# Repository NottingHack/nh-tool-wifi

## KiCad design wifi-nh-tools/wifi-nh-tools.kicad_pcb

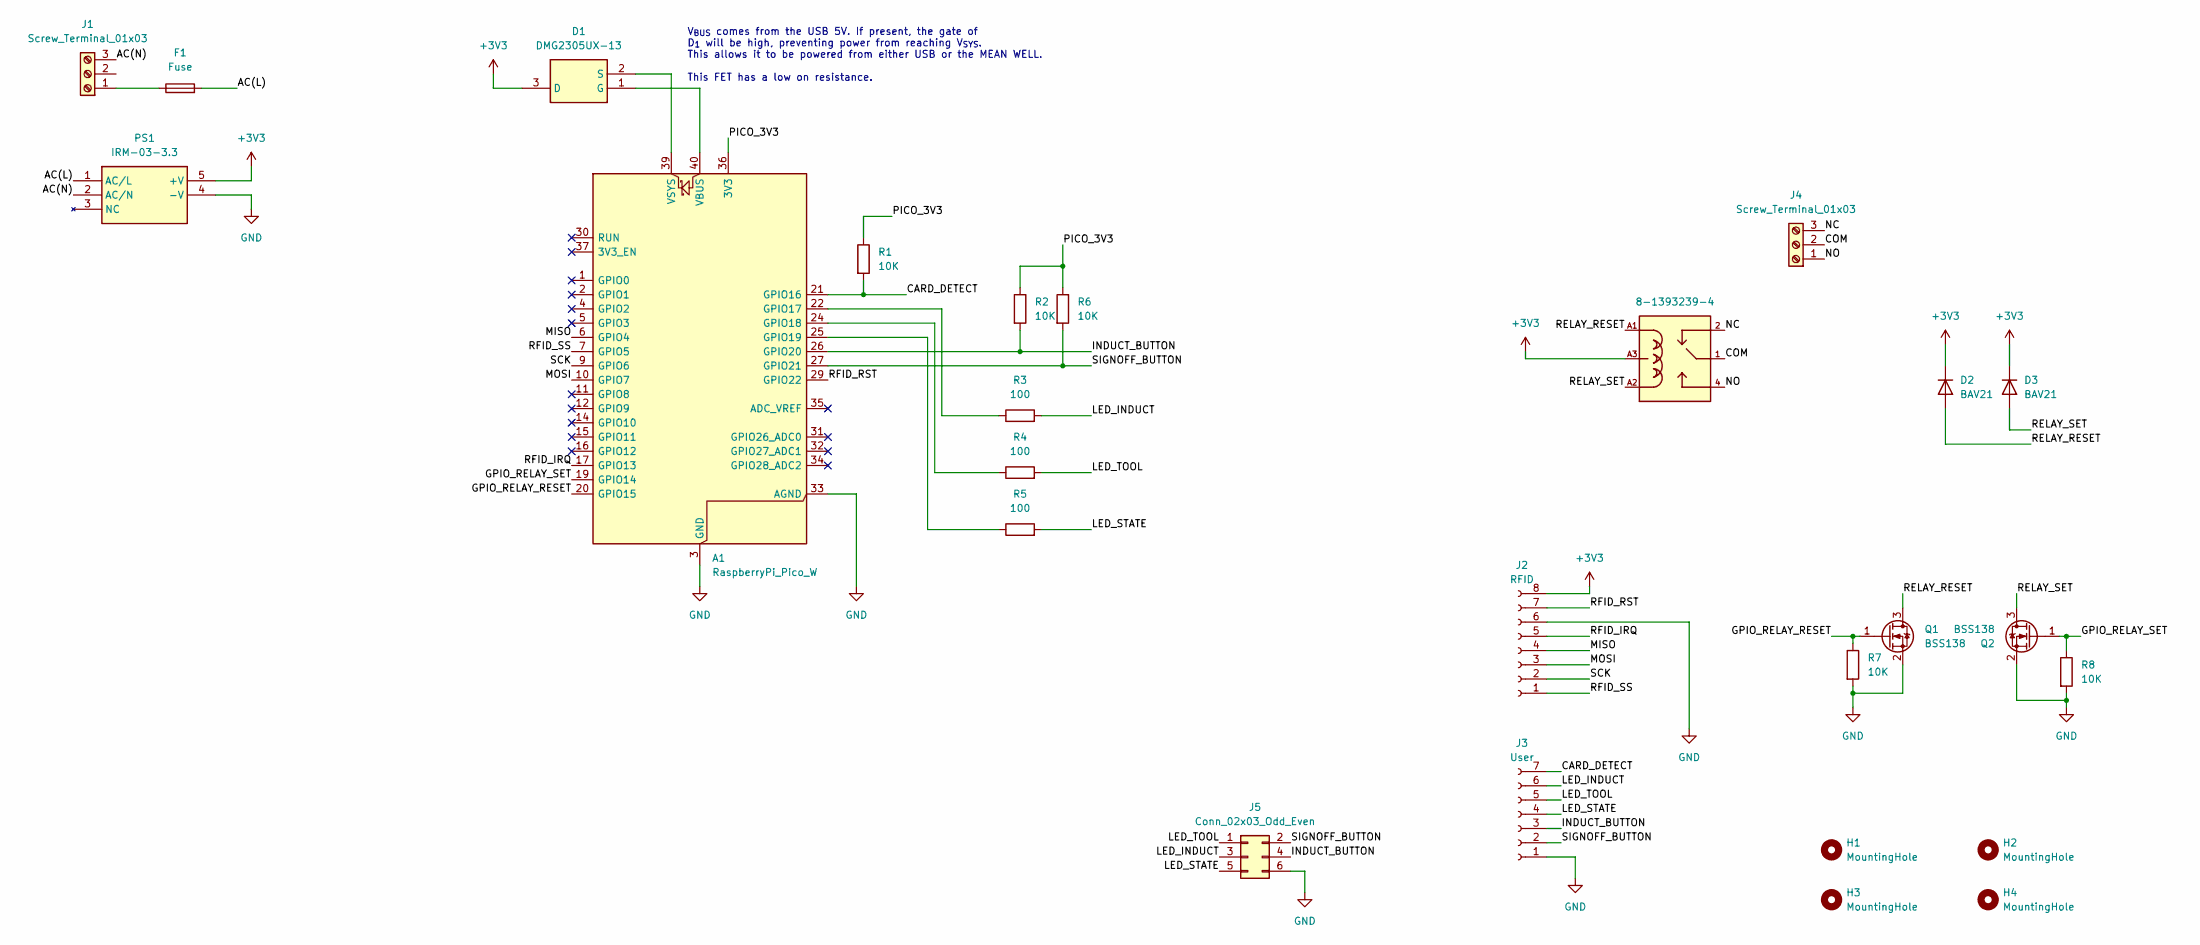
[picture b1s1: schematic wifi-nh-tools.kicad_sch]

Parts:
A1: RaspberryPi_Pico_W; RaspberryPi_Pico_W_SMD_HandSolder
D1: DMG2305UX-13; SOT96P240X120-3N; MPN DMG2305UX-13
D2, D3: BAV21; Nexperia_CFP3_SOD-123W; MPN BAV21WS-AQ
F1: Fuse; Fuse_Littelfuse-NANO2-462; MPN 0443002.DR
H1, H2, H3, H4: MountingHole; MountingHole_3.2mm_M3
J1, J4: Screw_Terminal_01x03; TerminalBlock_WAGO_2601-1103_1x03_P3.50mm_Horizontal; MPN 2601-1103
J2: RFID; PinSocket_1x08_P2.54mm_Vertical; MPN 61900811121
J3: User; PinSocket_1x07_P2.54mm_Vertical; MPN 61900811121
J5: Conn_02x03_Odd_Even; PinSocket_2x03_P2.54mm_Vertical; MPN 61303218421
K1: 8-1393239-4; TE_8-1393239-4; MPN 8-1393239-4
PS1: IRM-03-3.3; IRM035; MPN IRM-03-3.3
Q1, Q2: BSS138; SOT-23; MPN BSS138
R1, R2, R6: 10K; R_0603_1608Metric
R3, R4, R5: 100; R_0603_1608Metric
R7, R8: 10K; R_0603_1608Metric; MPN 560112116005

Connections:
+3V3: D1.3 (D), D2.1 (K), D3.1 (K), J2.8, K1.A3, PS1.5 (+V)
/AC(L): F1.2, PS1.1 (AC/L)
/AC(N): J1.3, PS1.2 (AC/N)
/CARD_DETECT: A1.21 (GPIO16), J3.7, R1.2
/COM: J4.2, K1.1, K1.11
/GPIO_RELAY_RESET: A1.20 (GPIO15), Q1.1 (G), R7.1
/GPIO_RELAY_SET: A1.19 (GPIO14), Q2.1 (G), R8.1
/INDUCT_BUTTON: A1.26 (GPIO20), J3.3, J5.4, R2.2
/LED_INDUCT: J3.6, J5.3, R3.2
/LED_STATE: J3.4, J5.5, R5.2
/LED_TOOL: J3.5, J5.1, R4.2
/MISO: A1.6 (GPIO4), J2.4
/MOSI: A1.10 (GPIO7), J2.3
/NC: J4.3, K1.2, K1.12
/NO: J4.1, K1.4, K1.14
/PICO_3V3: A1.36 (3V3), R1.1, R2.1, R6.1
/RELAY_RESET: D2.2 (A), K1.A1, Q1.3 (D)
/RELAY_SET: D3.2 (A), K1.A2, Q2.3 (D)
/RFID_IRQ: A1.17 (GPIO13), J2.5
/RFID_RST: A1.29 (GPIO22), J2.7
/RFID_SS: A1.7 (GPIO5), J2.1
/SCK: A1.9 (GPIO6), J2.2
/SIGNOFF_BUTTON: A1.27 (GPIO21), J3.2, J5.2, R6.2
GND: A1.3 (GND), A1.8 (GND), A1.13 (GND), A1.18 (GND), A1.23 (GND), A1.28 (GND), A1.33 (AGND), A1.38 (GND), J2.6, J3.1, J5.6, PS1.4 (-V), Q1.2 (S), Q2.2 (S), R7.2, R8.2
unnamed: A1.22 (GPIO17), R3.1
unnamed: A1.24 (GPIO18), R4.1
unnamed: A1.25 (GPIO19), R5.1
unnamed: A1.40 (VBUS), D1.1 (G)
unnamed: A1.39 (VSYS), D1.2 (S)
unnamed: F1.1, J1.1

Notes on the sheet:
V_{BUS} comes from the USB 5V. If present, the gate of D_{1} will be high, preventing power from reaching V_{SYS}. This allows it to be powered from either USB or the MEAN WELL. This FET has a low on resistance.

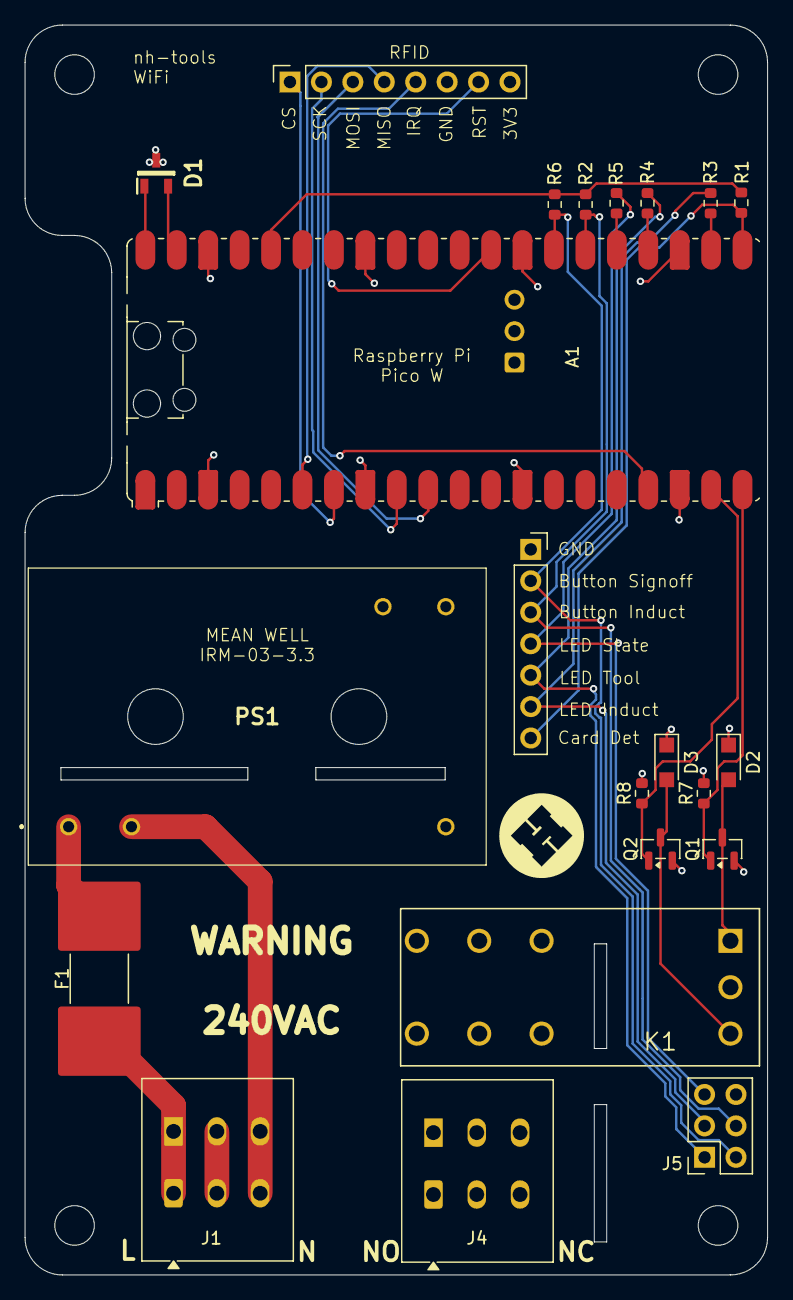
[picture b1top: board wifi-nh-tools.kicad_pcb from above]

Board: 4 copper layers, 60.0 x 101.0 mm, 26 parts (0 on the bottom side), 30 nets.

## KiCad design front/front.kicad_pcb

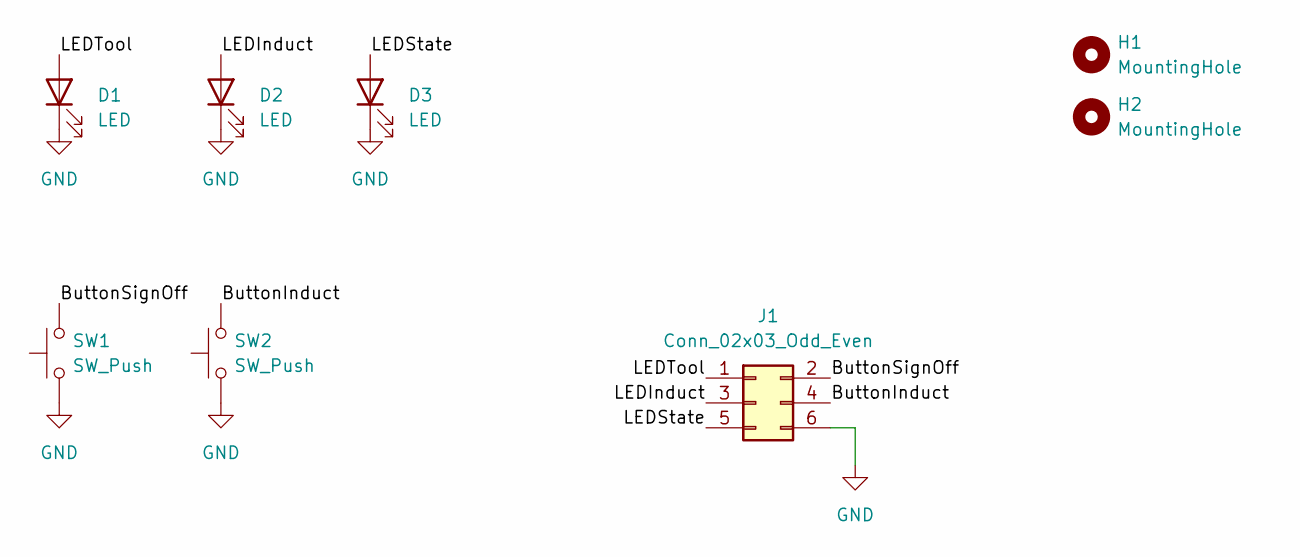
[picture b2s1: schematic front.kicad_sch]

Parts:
D1, D2, D3: LED; LED_D5.0mm
H1, H2: MountingHole; MountingHole_3.2mm_M3
J1: Conn_02x03_Odd_Even; PinHeader_2x03_P2.54mm_Vertical; MPN 61303218421
SW1, SW2: SW_Push; SW_PUSH_6mm

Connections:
/ButtonInduct: J1.4, SW2.2
/ButtonSignOff: J1.2, SW1.2
/LEDInduct: D2.2 (A), J1.3
/LEDState: D3.2 (A), J1.5
/LEDTool: D1.2 (A), J1.1
GND: D1.1 (K), D2.1 (K), D3.1 (K), J1.6, SW1.1, SW2.1

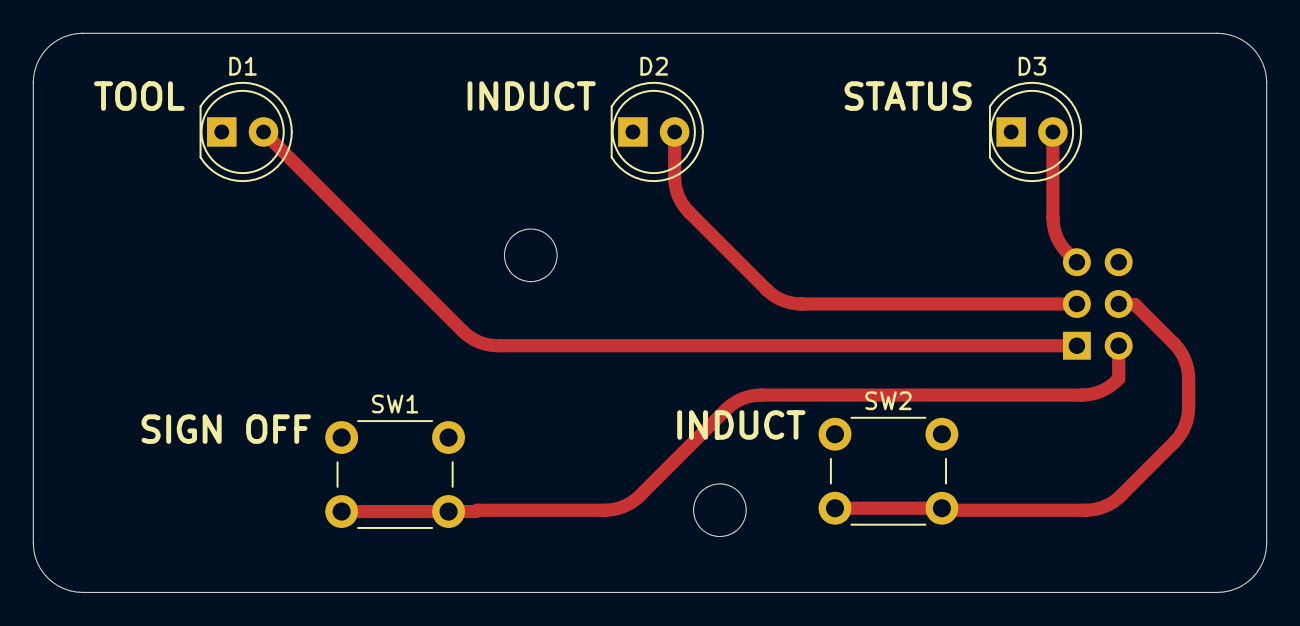
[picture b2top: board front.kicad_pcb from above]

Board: 2 copper layers, 75.0 x 34.0 mm, 8 parts (1 on the bottom side), 6 nets.

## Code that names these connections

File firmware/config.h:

#pragma once

#define WIFI_SSID ""
#define WIFI_PASSWORD ""

#define IP_ADDRESS ""
#define MQTT_ADDRESS ""
#define MQTT_BASE_TOPIC ""
#define TOOL_NAME ""

#define PIN_MISO 4
#define PIN_MOSI 7
#define PIN_SCK 6

#define PIN_RFID_SS 5
#define PIN_RFID_IRQ 13
#define PIN_RFID_RESET 22

#define PIN_RELAY_SET 14
#define PIN_RELAY_RESET 15

#define PIN_CARD_DETECT 16 // Not used
#define PIN_LED_INDUCT 17
#define PIN_LED_TOOL 18
#define PIN_LED_STATE 19
#define PIN_BUTTON_INDUCT 20
#define PIN_BUTTON_SIGNOFF 21

#define SESSION_TIMEOUT 15    // 15s - Session timout - how long to wait without seeing the card before disabling tool
#define AUTH_TIMEOUT 10       // How long in seconds to wait for AUTH response
#define INDUCT_TIMEOUT 30     // How long in seconds to wait for card when in the induct state
                              //
#define INDUCT_FLASH_FREQ 250 // how fast the induct led flashed after induct button pushed (lower is faster)
#define STATE_FLASH_FREQ  100 // Same again but for state LED

typedef struct
{
	int pin_number;
	int pin_dir;
	int initial_value;
} pin_config_t;

const pin_config_t pin_configs[] = {
	{ PIN_MISO,           GPIO_IN,     0 },
	{ PIN_MOSI,           GPIO_OUT,    0 },
	{ PIN_SCK,            GPIO_OUT,    0 },
	{ PIN_RFID_SS,        GPIO_OUT,    0 },
	{ PIN_RFID_IRQ,       GPIO_IN,     0 },
	{ PIN_RFID_RESET,     GPIO_OUT,    0 },
	{ PIN_RELAY_SET,      GPIO_OUT,    0 },
	{ PIN_RELAY_RESET,    GPIO_OUT,    0 },
	{ PIN_CARD_DETECT,    GPIO_IN,     0 },
	{ PIN_LED_INDUCT,     GPIO_OUT,    0 },
	{ PIN_LED_TOOL,       GPIO_OUT,    0 },
	{ PIN_LED_STATE,      GPIO_OUT,    0 },
	{ PIN_BUTTON_INDUCT,  GPIO_IN,     0 },
	{ PIN_BUTTON_SIGNOFF, GPIO_IN,     0 },
};
const int num_pin_configs = sizeof(pin_configs) / sizeof(pin_configs[0]);

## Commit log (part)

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2026-03-20 Hopefully the working enclosure...
2026-03-20 DTF image (for inkfuseuvdtf.co.uk)
2026-03-21 Fix solder mask on high current traces
2026-03-25 Add card holder
2026-03-28 Move gland opening away from edge
2026-03-28 starting the firmware...
2026-03-28 allow FreeCAD diffs
2026-03-28 add pico-mqtt lib
2026-03-28 Sort out FreeRTOS libraries
2026-03-28 skeleton
2026-03-28 more skeletons
2026-03-29 pico_lwip_mqtt seems more sensible
2026-04-01 Create a task to read the buttons, a task to drive the leds, and a test task to plumb their queues together.
2026-04-06 Working MFRC522 initialisation, lots of WIP
2026-04-06 Remove extra debug and excessive delays. Disable SPI debug.
2026-05-12 Working WiFi and MQTT initialisation. Scaffold for the state machine. Lots of mess to clean up.
2026-05-26 Implement a menu driven settings system using FLASH as nonvolatile storage. Add a modified linker script to reserve space at the end of FLASH for settings. Tidied up some old test code.
2026-05-26 Support for static IP address, with fallback to DHCP.
2026-05-26 Move DHCP / Static IP Logic to a more appropriate place.
